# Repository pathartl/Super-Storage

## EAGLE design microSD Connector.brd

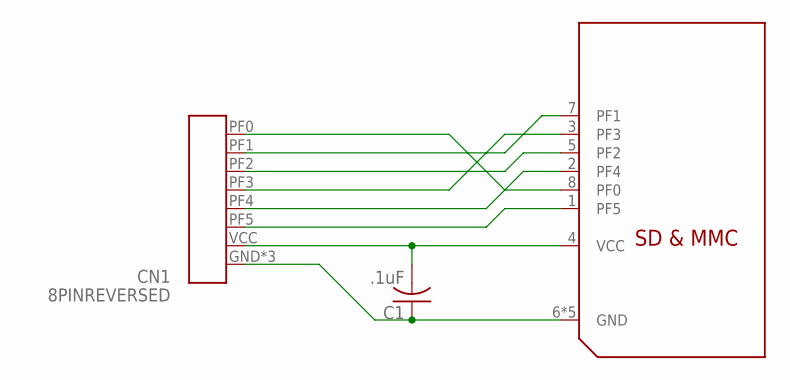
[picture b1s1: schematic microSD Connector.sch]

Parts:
C1: .1uF; C0805K
CN1: 8PINREVERSED; SFV8R-3STBE1HLF-REVERSED
U$1: MICROSD

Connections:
GND: C1.1, CN1.GND, CN1.GNDP1 (GND), CN1.GNDP2 (GND), U$1.6 (GND), U$1.CD1 (GND), U$1.CD2 (GND), U$1.MT1 (GND), U$1.MT2 (GND)
unnamed: CN1.PF0, U$1.8 (PF0)
unnamed: CN1.PF1, U$1.7 (PF1)
unnamed: CN1.PF2, U$1.5 (PF2)
unnamed: CN1.PF3, U$1.3 (PF3)
unnamed: CN1.PF4, U$1.2 (PF4)
unnamed: CN1.PF5, U$1.1 (PF5)
VCC: C1.2, CN1.VCC, U$1.4 (VCC)

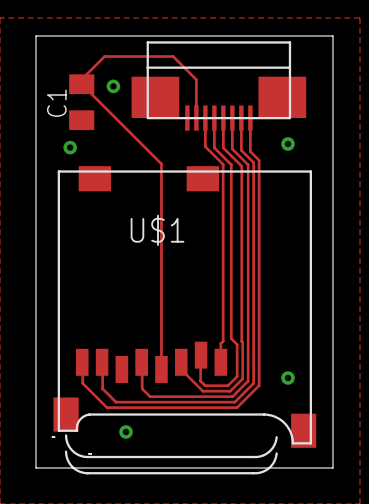
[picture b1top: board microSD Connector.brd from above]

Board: 2 copper layers, 16.5 x 24.0 mm, 3 parts (0 on the bottom side), 8 nets.

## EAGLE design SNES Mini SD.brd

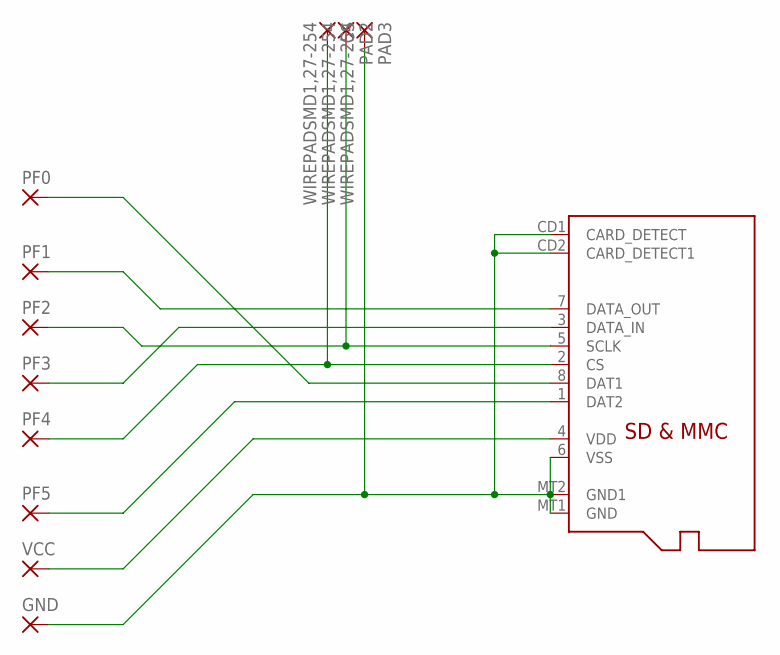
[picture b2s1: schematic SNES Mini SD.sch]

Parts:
CS: WIREPADSMD1,27-254; SMD1,27-2,54
GND: 2,15/1,0
PAD2, PAD3: WIREPADSMD1,27-254; SMD1,27-2,54
PF0, PF1, PF2, PF3, PF4, PF5: 2,15/1,0
U$1: MICROSD
VCC: 2,15/1,0

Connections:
GND: GND.1, PAD3.1, U$1.6 (VSS), U$1.CD1 (CARD_DETECT), U$1.CD2 (CARD_DETECT1), U$1.MT1 (GND), U$1.MT2 (GND1)
unnamed: PF0.1, U$1.8 (DAT1)
unnamed: PF1.1, U$1.7 (DATA_OUT)
PF2: PAD2.1, PF2.1, U$1.5 (SCLK)
PF3: PF3.1, U$1.3 (DATA_IN)
PF4: CS.1, PF4.1, U$1.2 (CS)
PF5: PF5.1, U$1.1 (DAT2)
VDD: U$1.4 (VDD), VCC.1

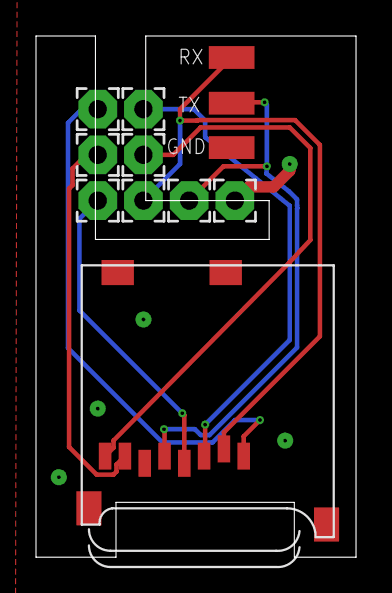
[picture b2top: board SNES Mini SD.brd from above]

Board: 2 copper layers, 17.8 x 29.0 mm, 12 parts (0 on the bottom side), 8 nets.

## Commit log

2018-04-07 Rev 1
2020-12-27 Create LICENSE
2020-12-27 Latest revision. Labeled as Rev 2, but is closer to rev 3.

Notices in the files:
microSD Connector.brd:
Copyright 2018
